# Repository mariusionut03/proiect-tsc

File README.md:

# OpenBook e-book reader

## BOM - Bill of Materials

| Device Module                       | Amount | Datasheet | Shop |
| ----------------------------------- | ------ | -------| --------|
| 112A-TAAR-R03_ATTEND                | 1      | https://www.attend.com.tw/en/product.php?act=view&id=253 | https://www.digikey.com/en/products/detail/attend-technology/112A-TAAR-R03/17633923 |
| BD5229G-TR                          | 1      | https://www.digikey.ph/en/products/detail/rohm-semiconductor/BD5229G-TR/658502 | https://www.digikey.ph/en/products/detail/rohm-semiconductor/BD5229G-TR/658502 |
| BUTTON_COSYOMV1                     | 3      | https://components101.com/switches/push-button | https://uk.farnell.com/wurth-elektronik/430182043816/switch-160gf-6x6mm-smd-4-3mm-act/dp/2065105?CMP=GRHB-OEMSECRETS101 |
| CPH3225A                            | 1      | https://www.digikey.com/en/products/detail/seiko-instruments/CPH3225A/8692444 | https://www.digikey.com/en/products/detail/seiko-instruments/CPH3225A/8692444 |
| DS3231SN                            | 1      | https://www.digikey.com/en/products/detail/analog-devices-inc-maxim-integrated/DS3231SN/1197576 | https://www.digikey.com/en/products/detail/analog-devices-inc-maxim-integrated/DS3231SN/1197576 |
| BME680                              | 1      | https://www.sparkfun.com/sparkfun-environmental-sensor-breakout-bme680-qwiic.html | https://www.sparkfun.com/sparkfun-environmental-sensor-breakout-bme680-qwiic.html |
| MCP73831                            | 1      | https://www.microchip.com/en-us/product/mcp73831 | https://www.microchipdirect.com/product/MCP73831T-2ADI/OT |
| C6-WROOM-1-N8                       | 1      | https://www.espressif.com/sites/default/files/documentation/esp32-c6-wroom-1_wroom-1u_datasheet_en.pdf | https://www.adafruit.com/product/5671 |
| FH34SRJ-24S-0.5SH_99_               | 1      | https://www.hirose.com/product/p/CL0580-1255-6-99 | https://www.hirose.com/product/p/CL0580-1255-6-99 |
| MAX17048G+T10                       | 1      | https://eu.mouser.com/ProductDetail/Analog-Devices-Maxim-Integrated/MAX17048G+T10?qs=D7PJwyCwLAoGnnn8jEPRBQ%3D%3D | https://eu.mouser.com/ProductDetail/Analog-Devices-Maxim-Integrated/MAX17048G+T10?qs=D7PJwyCwLAoGnnn8jEPRBQ%3D%3D |
| MBR0530                             | 3      | https://www.digikey.com/en/products/detail/onsemi/MBR0530/1048783 | https://www.digikey.com/en/products/detail/onsemi/MBR0530/1048783 |
| PGB1010603MR                        | 6      | https://www.digikey.com/en/products/detail/littelfuse-inc/PGB1010603MR/715755 | https://www.digikey.com/en/products/detail/littelfuse-inc/PGB1010603MR/715755 |
| SAMACSYS_PARTS_USB4110-GF-A         | 1      | https://www.digikey.ro/en/products/detail/gct/USB4110-GF-A/10384547 | https://www.digikey.ro/en/products/detail/gct/USB4110-GF-A/10384547 |
| SI1308EDL-T1-GE3                    | 1      | https://www.digikey.com/en/products/detail/vishay-siliconix/SI1308EDL-T1-GE3/4876435 | https://www.digikey.com/en/products/detail/vishay-siliconix/SI1308EDL-T1-GE3/4876435 |
| SJ                                  | 1      | https://www.digikey.com/en/products/detail/cui-devices/SJ1-3514N/738685 | https://www.digikey.com/en/products/detail/cui-devices/SJ1-3514N/738685 |
| USBLC6-2SC6Y                        | 1      | https://www.digikey.com/en/products/detail/stmicroelectronics/USBLC6-2SC6Y/2819177 | https://www.digikey.com/en/products/detail/stmicroelectronics/USBLC6-2SC6Y/2819177 |
| W25Q512JVEIQ                        | 1      | https://www.digikey.com/en/products/detail/winbond-electronics/W25Q512JVEIQ/10244706 | https://www.digikey.com/en/products/detail/winbond-electronics/W25Q512JVEIQ/10244706 |
| XC6220A331MR-G                      | 1      | https://www.digikey.com/en/products/detail/torex-semiconductor-ltd/XC6220B331MR-G/2138177 | https://www.digikey.com/en/products/detail/torex-semiconductor-ltd/XC6220B331MR-G/2138177 |
| SD0805S020S1R0                      | 2      | https://www.digikey.com/en/products/detail/kyocera-avx/SD0805S020S1R0/3749517 | https://www.digikey.com/en/products/detail/kyocera-avx/SD0805S020S1R0/3749517 |
| LTSPICE_C 100nF                     | 8      | https://www.digikey.com/en/products/detail/nextgen-components/0402B104K500HI/22601924 | https://www.digikey.com/en/products/detail/nextgen-components/0402B104K500HI/22601924 |
| LTSPICE_C 10nF                      | 1      | https://www.amazon.com/ALLECIN-Electrolytic-Capacitor-0-2x0-43in-Capacitors/dp/B0CMQC587X/ref=sr_1_1_sspa?sr=8-1-spons&sp_csd=d2lkZ2V0TmFtZT1zcF9hdGY&psc=1 | https://www.amazon.com/ALLECIN-Electrolytic-Capacitor-0-2x0-43in-Capacitors/dp/B0CMQC587X/ref=sr_1_1_sspa?sr=8-1-spons&sp_csd=d2lkZ2V0TmFtZT1zcF9hdGY&psc=1 |
| LTSPICE_C 4.7uF                     | 6      | https://www.amazon.com/ALLECIN-Electrolytic-Capacitor-0-2x0-43in-Capacitors/dp/B0CMQC587X/ref=sr_1_1_sspa?sr=8-1-spons&sp_csd=d2lkZ2V0TmFtZT1zcF9hdGY&psc=1 | https://www.amazon.com/ALLECIN-Electrolytic-Capacitor-0-2x0-43in-Capacitors/dp/B0CMQC587X/ref=sr_1_1_sspa?sr=8-1-spons&sp_csd=d2lkZ2V0TmFtZT1zcF9hdGY&psc=1 |
| LTSPICE_C 1uF                       | 10     | https://www.amazon.com/ALLECIN-Electrolytic-Capacitor-0-2x0-43in-Capacitors/dp/B0CMQC587X/ref=sr_1_1_sspa?sr=8-1-spons&sp_csd=d2lkZ2V0TmFtZT1zcF9hdGY&psc=1 | https://www.amazon.com/ALLECIN-Electrolytic-Capacitor-0-2x0-43in-Capacitors/dp/B0CMQC587X/ref=sr_1_1_sspa?sr=8-1-spons&sp_csd=d2lkZ2V0TmFtZT1zcF9hdGY&psc=1 |
| LTSPICE_C 0.1uF                     | 1      | https://www.digikey.com/en/products/detail/samsung-electro-mechanics/CL10E104KC8VPNC/20498486 | https://www.digikey.com/en/products/detail/samsung-electro-mechanics/CL10E104KC8VPNC/20498486 |
| ADAFRUIT_LED                        | 1      | https://www.adafruit.com/product/4684 | https://www.adafruit.com/product/4684 |
| ESP32_VARISTOR                      | 1      | https://uk.rs-online.com/web/p/varistors/9012743 | https://uk.rs-online.com/web/p/varistors/9012743 |
| CT3528 (RCL_CPOL-EU) 100uF          | 1      | https://www.datasheetarchive.com/?q=ct3528 |  |
| DMG2305UX-7 20V/4.2A/52mO/1.4W      | 2      | https://www.digikey.com/en/products/detail/diodes-incorporated/DMG2305UX-7/4340667 | https://www.digikey.com/en/products/detail/diodes-incorporated/DMG2305UX-7/4340667 |
| IND-4828-WE-TPC-WRE                 | 1      | https://www.axel-gl.com/en/asone/d/64-0172-48/ | https://www.axel-gl.com/en/asone/d/64-0172-48/ |
| JS-1MM(QWIIC_CONNECTOR)             | 1      | https://www.sparkfun.com/qwiic-jst-connector-smd-4-pin-horizontal.html | https://www.sparkfun.com/qwiic-jst-connector-smd-4-pin-horizontal.html |
| LTSPICE_R 5k1                       | 2      |  | https://www.amazon.com/BOJACK-Values-Resistor-Resistors-Assortment/dp/B08FD1XVL6/ref=sr_1_1_sspa?sr=8-1-spons&sp_csd=d2lkZ2V0TmFtZT1zcF9hdGY |
| LTSPICE_R 100k                      | 1      |  | https://www.amazon.com/BOJACK-Values-Resistor-Resistors-Assortment/dp/B08FD1XVL6/ref=sr_1_1_sspa?sr=8-1-spons&sp_csd=d2lkZ2V0TmFtZT1zcF9hdGY |
| LTSPICE_R 2.2                       | 1      |  | https://www.amazon.com/BOJACK-Values-Resistor-Resistors-Assortment/dp/B08FD1XVL6/ref=sr_1_1_sspa?sr=8-1-spons&sp_csd=d2lkZ2V0TmFtZT1zcF9hdGY |
| LTSPICE_R 10k                       | 16     |  | https://www.amazon.com/BOJACK-Values-Resistor-Resistors-Assortment/dp/B08FD1XVL6/ref=sr_1_1_sspa?sr=8-1-spons&sp_csd=d2lkZ2V0TmFtZT1zcF9hdGY |
| LTSPICE_R 0.47                      | 1      |  | https://www.amazon.com/BOJACK-Values-Resistor-Resistors-Assortment/dp/B08FD1XVL6/ref=sr_1_1_sspa?sr=8-1-spons&sp_csd=d2lkZ2V0TmFtZT1zcF9hdGY |
| LTSPICE_R 2k                        | 1      |  | https://www.amazon.com/BOJACK-Values-Resistor-Resistors-Assortment/dp/B08FD1XVL6/ref=sr_1_1_sspa?sr=8-1-spons&sp_csd=d2lkZ2V0TmFtZT1zcF9hdGY |
| LTSPICE_R 200                       | 1      |  | https://www.amazon.com/BOJACK-Values-Resistor-Resistors-Assortment/dp/B08FD1XVL6/ref=sr_1_1_sspa?sr=8-1-spons&sp_csd=d2lkZ2V0TmFtZT1zcF9hdGY |
| LTSPICE_R 15                        | 1      |  | https://www.amazon.com/BOJACK-Values-Resistor-Resistors-Assortment/dp/B08FD1XVL6/ref=sr_1_1_sspa?sr=8-1-spons&sp_csd=d2lkZ2V0TmFtZT1zcF9hdGY |
| Test Pad TP20R                      | 17     | https://us.misumi-ec.com/vona2/detail/221005496391/?HissuCode=TP20R-24 | https://us.misumi-ec.com/vona2/detail/221005496391/?HissuCode=TP20R-24 |

## ESP32-C6

- EN - RESET (Activare sau dezactivare device)
- IO0 - INT_RTC (Pin pentru intrerupere ale ceasului RTC sau Real Time Clock)
- IO1 - 32KHZ (Ofera o frecventa de 32 kHz, utilizata pentru sincronizare.)
- IO2 - MISO (Master In Slave Out, comunicare SPI pentru primire date de la periferice)
- IO3 - EPD_BUSY (Indica starea ecranului: ocupat sau liber)
- IO4 - SS_SD (Activeaza cardul SD, Slave Select)
- IO5 - EPD_DC (Control pentru date si comenzi ecran)
- IO6 - SCK (Serial Clock)
- IO7 - MOSI (Master Out Slave In, comunicare SPI pentru trimitere date la periferice)
- IO8 - GPIO8
- IO9 - IO/BOOT (Schimbare state dispozitiv)
- IO10 - EPD_CS (Select display)
- IO11 - FLASH_CS (Select memoria Flash)
- IO12 - USB_D- (comunicare USB)
- IO13 - USB_D+ (comunicare USB)
- IO15 - IO/CHANGE (navigare)
- IO16 - TX (Transmitere date)
- IO17 - RX (Receptie date)
- IO18 - RTC_RST (Reset RTC)
- IO19 - I2C_PW (Linia de alimentare pentru periferice I2C)
- IO20 - EPD_3V3_C (Alimentare)
- IO21 - SDA (I2C Data)
- IO22 - SCL (I2C Clock)
- IO23 - EPD_RST (Reset display)
- GND - Connected to ground 

## Randari

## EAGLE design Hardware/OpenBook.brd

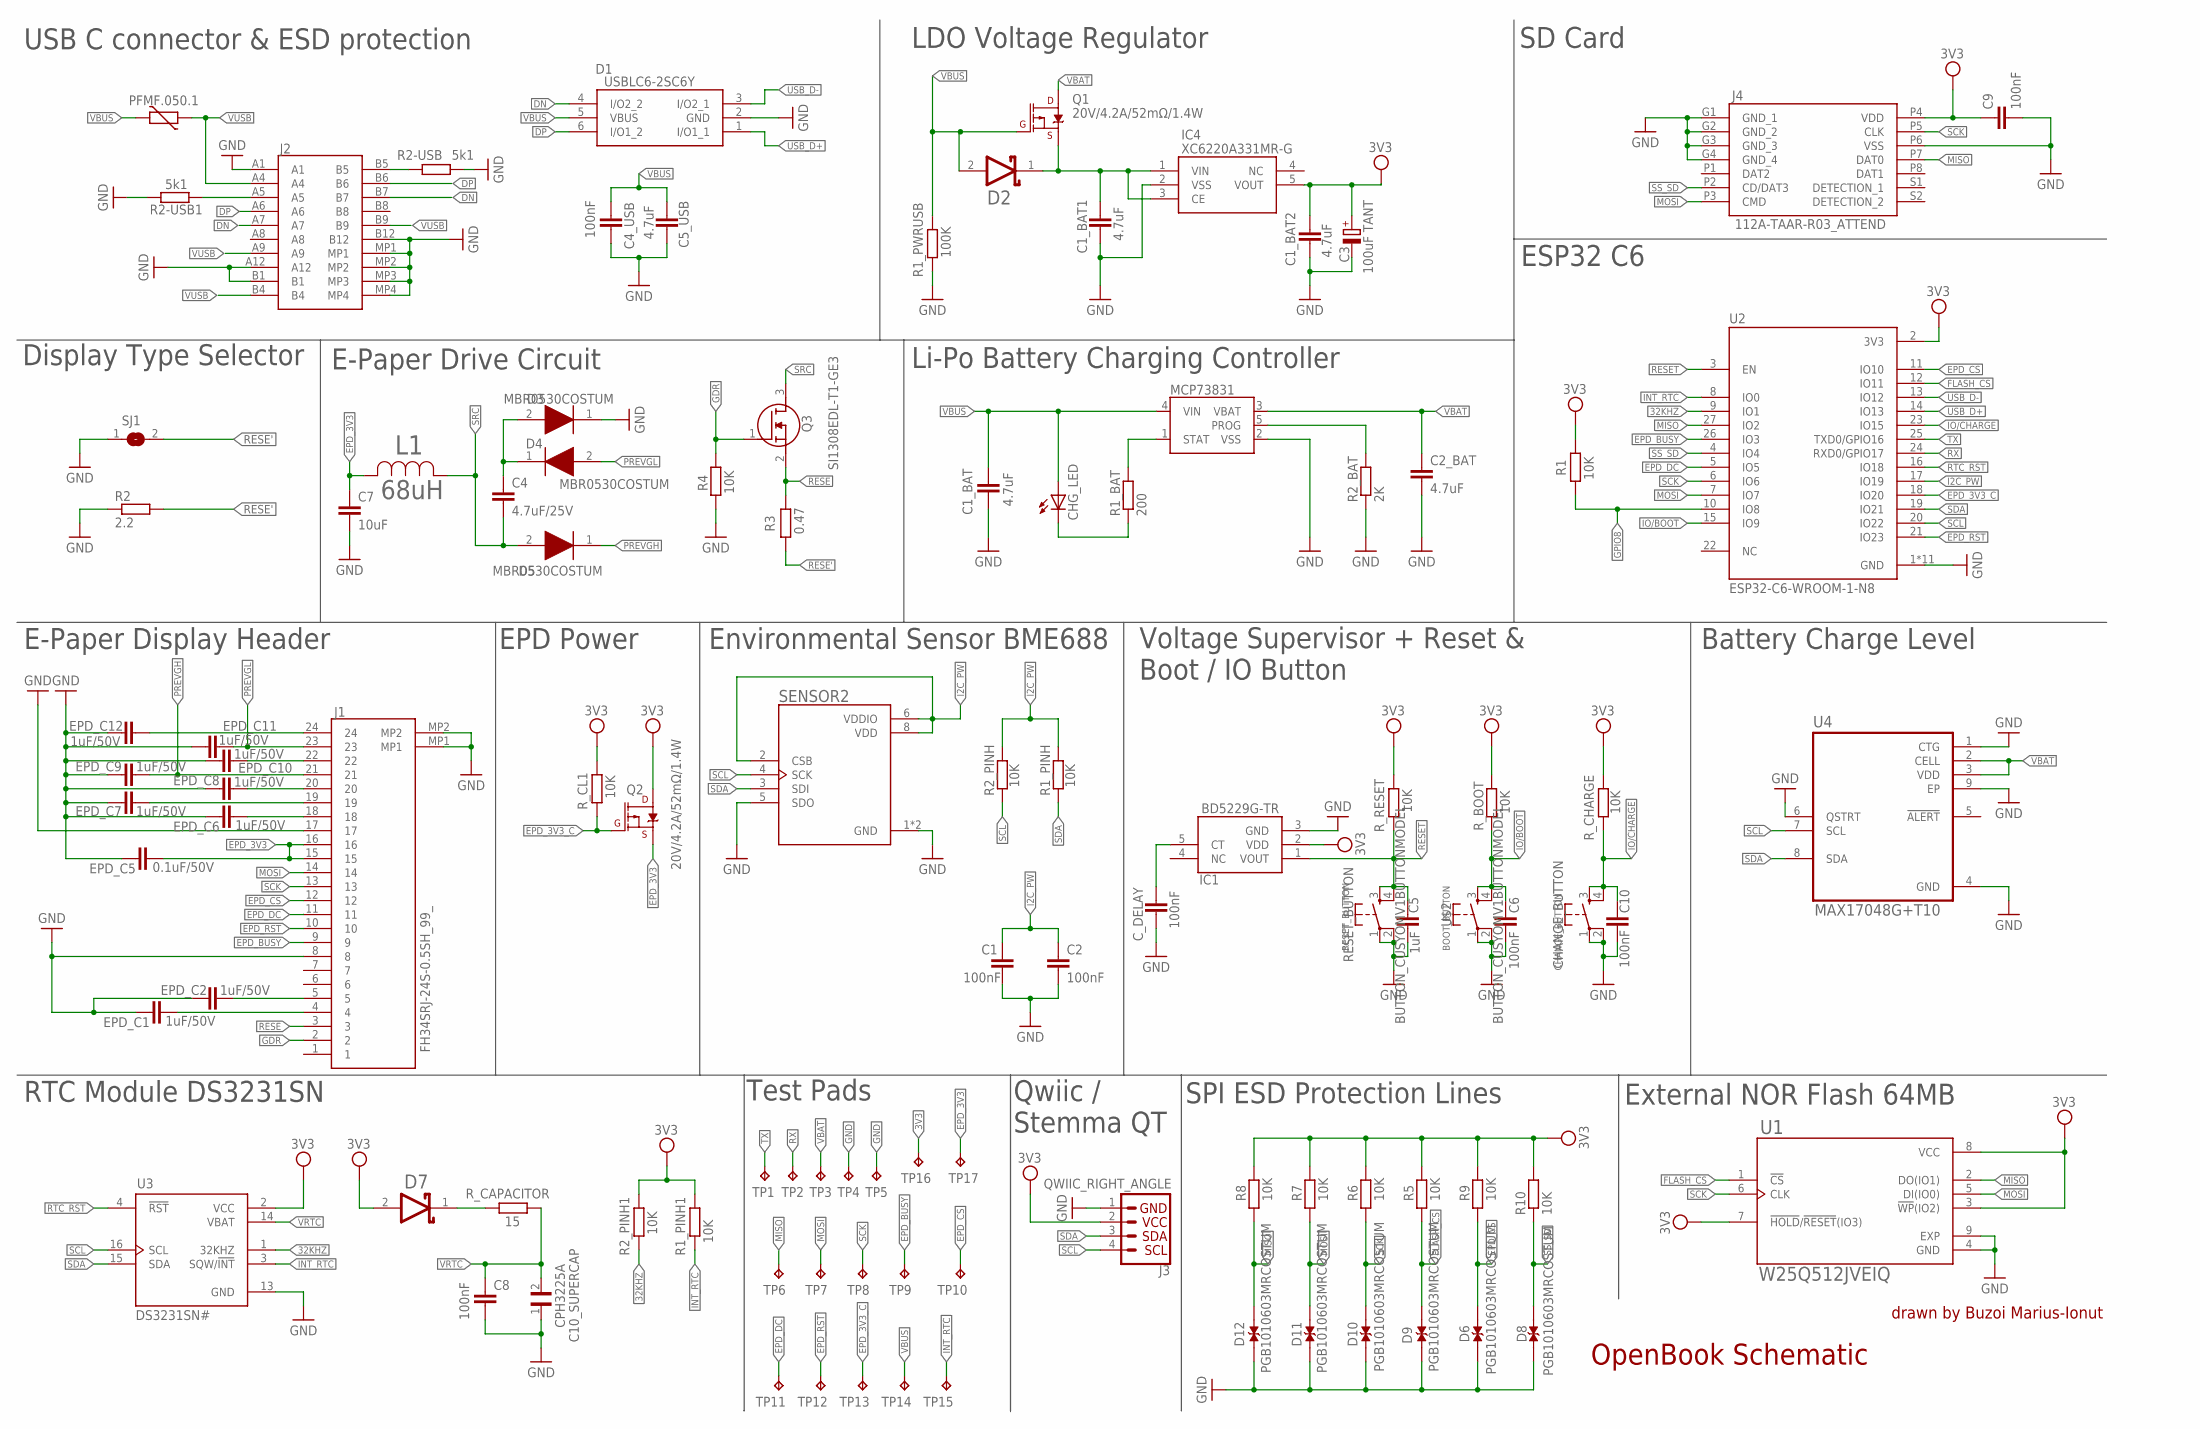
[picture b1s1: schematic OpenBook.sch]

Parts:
C1, C2, C4_USB, C6, C8, C9, C10: 100nF; ESP32_WROVER_EAGLE-LTSPICE_C0402
C1_BAT, C1_BAT1, C1_BAT2, C2_BAT, C5_USB: 4.7uF; ESP32_WROVER_EAGLE-LTSPICE_C0402
C3: 100uF TANT; RCL_CT3528
C4: 4.7uF/25V; ESP32_WROVER_EAGLE-LTSPICE_C0402
C5: 1uF; ESP32_WROVER_EAGLE-LTSPICE_C0402
C7: 10uF; ESP32_WROVER_EAGLE-LTSPICE_C0402
C10_SUPERCAP: CPH3225A; CAPCP3225X100N
CHANGE_BUTTON: BUTTON_CUSYOMV1BUTTONMODEL; MYBUTTON
CHG_LED: ADAFRUIT_LEDCHIP-LED0603; ADAFRUIT_CHIP-LED0603
C_DELAY: 100nF; ESP32_WROVER_EAGLE-LTSPICE_C0402
D1: USBLC6-2SC6Y; SOT95P280X145-6N
D2, D7: ESP32_WROVER_AVX---SD0805S020S1R0_AVX_SD0805S020S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; ESP32_WROVER_AVX---SD0805S020S1R0_AVX_SD0805S020S1R0_0
D3, D4, D5: MBR0530COSTUM; SOD3716X135N
D6, D8, D9, D10, D11, D12: PGB1010603MRCOSTUM; DIOC1608X36N
EPD_C1, EPD_C2, EPD_C6, EPD_C7, EPD_C8, EPD_C9, EPD_C10, EPD_C11, EPD_C12: 1uF/50V; ESP32_WROVER_EAGLE-LTSPICE_C0402
EPD_C5: 0.1uF/50V; ESP32_WROVER_EAGLE-LTSPICE_C0402
IC1: BD5229G-TR; SOT95P280X125-5N
IC4: XC6220A331MR-G; SOT95P280X120-5N
J1: FH34SRJ-24S-0.5SH_99_; FH34SRJ24S05SH99
J2: SAMACSYS_PARTS_USB4110-GF-A; SAMACSYS_PARTS_USB4110GFA
J3: QWIIC_RIGHT_ANGLE; JST04_1MM_RA
J4: 112A-TAAR-R03_ATTEND; 112ATAARR03ATTEND
L1: 68uH; IND_4828-WE-TPC_WRE
MCP73831: ESP32_WROVER_SPARKFUN-IC-POWER_MCP73831; ESP32_WROVER_SPARKFUN-IC-POWER_SOT23-5
PFMF.050.1: ESP32C6_VARISTORCN1812; ESP32C6_VARISTOR_CT/CN1812
Q1, Q2: 20V/4.2A/52mΩ/1.4W; ESP32_WROVER_SPARKFUN-DISCRETESEMI_SOT23-3
Q3: SI1308EDL-T1-GE3; SOT65P210X110-3N
R1, R1_PINH, R1_PINH1, R2_PINH, R2_PINH1, R4, R5, R6, R7, R8, R9, R10: 10K; ESP32_WROVER_EAGLE-LTSPICE_R0402
R1_BAT: 200; ESP32_WROVER_EAGLE-LTSPICE_R0402
R1_PWRUSB: 100K; ESP32_WROVER_EAGLE-LTSPICE_R0402
R2: 2.2; ESP32_WROVER_EAGLE-LTSPICE_R0402
R2-USB, R2-USB1: 5k1; ESP32_WROVER_EAGLE-LTSPICE_R0402
R2_BAT: 2K; ESP32_WROVER_EAGLE-LTSPICE_R0402
R3: 0.47; ESP32_WROVER_EAGLE-LTSPICE_R0402
RESET_BUTTON: BUTTON_CUSYOMV1BUTTONMODEL; MYBUTTON
R_BOOT: 10K; ESP32_WROVER_EAGLE-LTSPICE_R0402
R_CAPACITOR: 15; ESP32_WROVER_EAGLE-LTSPICE_R0402
R_CHARGE: 10K; ESP32_WROVER_EAGLE-LTSPICE_R0402
R_CL1: 10K; ESP32_WROVER_EAGLE-LTSPICE_R0402
R_RESET: 10K; ESP32_WROVER_EAGLE-LTSPICE_R0402
SENSOR2: ESP32_WROVER_BME680_BME680; ESP32_WROVER_BME680_PSON80P300X300X100-8N
SJ1: SJ
TP1, TP2, TP3, TP4, TP5, TP6, TP7, TP8, TP9, TP10, TP11, TP12, TP13, TP14, TP15, TP16, TP17: TP; TP20R
U1: W25Q512JVEIQ; SON127P600X800X80-9N
U2: ESP32-C6-WROOM-1-N8; XCVR_ESP32-C6-WROOM-1-N8
U3: DS3231SN#; SOIC127P1032X265-16N
U4: MAX17048G+T10; SON50P200X200X80-9N
U$2: BUTTON_CUSYOMV1BUTTONMODEL; MYBUTTON

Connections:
3V3: C1_BAT2.1, C3.+, C9.1, D7.2 (ANODE), IC1.2 (VDD), IC4.5 (VOUT), J3.2, J4.P4 (VDD), Q2.3 (D), R1.2, R1_PINH1.2, R2_PINH1.2, R5.2, R6.2, R7.2, R8.2, R9.2, R10.2, R_BOOT.2, R_CHARGE.2, R_CL1.2, R_RESET.2, TP16.TP, U1.3 (!WP!(IO2)), U1.7 (!HOLD!/!RESET!(IO3)), U1.8 (VCC), U2.2 (3V3), U3.2 (VCC)
32KHZ: R2_PINH1.1, U2.9 (IO1), U3.1 (32KHZ)
DN: D1.4 (I/O2_2), J2.A7, J2.B7
DP: D1.6 (I/O1_2), J2.A6, J2.B6
EPD_3V3: C7.1, EPD_C5.2, J1.15, J1.16, L1.2, Q2.2 (S), TP17.TP
EPD_3V3_C: Q2.1 (G), R_CL1.1, TP13.TP, U2.18 (IO20)
EPD_BUSY: J1.9, TP9.TP, U2.26 (IO3)
EPD_CS: D6.2, J1.12, R9.1, TP10.TP, U2.11 (IO10)
EPD_DC: J1.11, TP11.TP, U2.5 (IO5)
EPD_RST: J1.10, TP12.TP, U2.21 (IO23)
FLASH_CS: D9.2, R5.1, U1.1 (!CS), U2.12 (IO11)
GDR: J1.2, Q3.1 (G), R4.2
GND: C1.2, C1_BAT.2, C1_BAT1.2, C1_BAT2.2, C2.2, C2_BAT.2, C3.-, C4_USB.2, C5.2, C5_USB.2, C6.2, C7.2, C8.2, C9.2, C10.2, C10_SUPERCAP.1, CHANGE_BUTTON.1, CHANGE_BUTTON.2, C_DELAY.2, D1.2 (GND), D3.1 (K), D6.1, D8.1, D9.1, D10.1, D11.1, D12.1, EPD_C1.1, EPD_C2.1, EPD_C5.1, EPD_C6.1, EPD_C7.1, EPD_C8.1, EPD_C9.1, EPD_C10.1, EPD_C11.1, EPD_C12.1, IC1.3 (GND), IC4.2 (VSS), J1.8, J1.17, J1.MP1, J1.MP2, J2.A1, J2.A12, J2.B1, J2.B12, J2.MP1, J2.MP2, J2.MP3, J2.MP4, J3.1, J4.G1 (GND_1), J4.G2 (GND_2), J4.G3 (GND_3), J4.G4 (GND_4), J4.P6 (VSS), MCP73831.2 (VSS), R1_PWRUSB.1, R2.1, R2-USB.2, R2-USB1.1, R2_BAT.1, R4.1, RESET_BUTTON.1, RESET_BUTTON.2, SENSOR2.1 (GND), SENSOR2.5 (SDO), SENSOR2.7 (GND), SJ1.1, TP4.TP, TP5.TP, U1.4 (GND), U1.9 (EXP), U2.1 (GND), U2.28 (GND), U2.29_1 (GND), U2.29_2 (GND), U2.29_3 (GND), U2.29_4 (GND), U2.29_5 (GND), U2.29_6 (GND), U2.29_7 (GND), U2.29_8 (GND), U2.29_9 (GND), U3.13 (GND), U4.1 (CTG), U4.4 (GND), U4.6 (QSTRT), U4.9 (EP), U$2.1, U$2.2
GPIO8: R1.1, U2.10 (IO8)
I2C_PW: C1.1, C2.1, R1_PINH.2, R2_PINH.2, SENSOR2.2 (CSB), SENSOR2.6 (VDDIO), SENSOR2.8 (VDD), U2.17 (IO19)
INT_RTC: R1_PINH1.1, TP15.TP, U2.8 (IO0), U3.3 (SQW/!INT)
IO/BOOT: C6.1, R_BOOT.1, U2.15 (IO9), U$2.3, U$2.4
IO/CHARGE: C10.1, CHANGE_BUTTON.3, CHANGE_BUTTON.4, R_CHARGE.1, U2.23 (IO15)
MISO: D12.2, J4.P7 (DAT0), R8.1, TP6.TP, U1.2 (DO(IO1)), U2.27 (IO2)
MOSI: D11.2, J1.14, J4.P3 (CMD), R7.1, TP7.TP, U1.5 (DI(IO0)), U2.7 (IO7)
unnamed: J2.A5, R2-USB1.2
unnamed: C1_BAT1.1, D2.1 (CATHODE), IC4.1 (VIN), IC4.3 (CE), Q1.2 (S)
unnamed: MCP73831.1 (STAT), R1_BAT.2
unnamed: J2.B5, R2-USB.1
unnamed: CHG_LED.C, R1_BAT.1
unnamed: C4.1, D3.2 (A), D4.1 (K)
unnamed: EPD_C12.2, J1.24
unnamed: MCP73831.5 (PROG), R2_BAT.2
unnamed: C_DELAY.1, IC1.5 (CT)
unnamed: EPD_C10.2, J1.22
unnamed: EPD_C8.2, J1.20
unnamed: D7.1 (CATHODE), R_CAPACITOR.1
unnamed: EPD_C7.2, J1.19
unnamed: EPD_C6.2, J1.18
unnamed: EPD_C2.2, J1.5
unnamed: EPD_C1.2, J1.4
PREVGH: D5.1 (K), EPD_C9.2, J1.21
PREVGL: D4.2 (A), EPD_C11.2, J1.23
RESE: J1.3, Q3.2 (S), R3.2
RESE': R2.2, R3.1, SJ1.2
RESET: C5.1, IC1.1 (VOUT), RESET_BUTTON.3, RESET_BUTTON.4, R_RESET.1, U2.3 (EN)
RTC_RST: U2.16 (IO18), U3.4 (!RST)
RX: TP2.TP, U2.24 (RXD0/GPIO17)
SCK: D10.2, J1.13, J4.P5 (CLK), R6.1, TP8.TP, U1.6 (CLK), U2.6 (IO6)
SCL: J3.4, R2_PINH.1, SENSOR2.4 (SCK), U2.20 (IO22), U3.16 (SCL), U4.7 (SCL)
SDA: J3.3, R1_PINH.1, SENSOR2.3 (SDI), U2.19 (IO21), U3.15 (SDA), U4.8 (SDA)
SRC: C4.2, D5.2 (A), L1.1, Q3.3 (D)
SS_SD: D8.2, J4.P2 (CD/DAT3), R10.1, U2.4 (IO4)
TX: TP1.TP, U2.25 (TXD0/GPIO16)
USB_D+: D1.1 (I/O1_1), U2.14 (IO13)
USB_D-: D1.3 (I/O2_1), U2.13 (IO12)
VBAT: C2_BAT.1, MCP73831.3 (VBAT), Q1.3 (D), TP3.TP, U4.2 (CELL), U4.3 (VDD)
VBUS: C1_BAT.1, C4_USB.1, C5_USB.1, CHG_LED.A, D1.5 (VBUS), D2.2 (ANODE), MCP73831.4 (VIN), PFMF.050.1.2, Q1.1 (G), R1_PWRUSB.2, TP14.TP
VRTC: C8.1, C10_SUPERCAP.2, R_CAPACITOR.2, U3.14 (VBAT)
VUSB: J2.A4, J2.A9, J2.B4, J2.B9, PFMF.050.1.1

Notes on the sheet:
drawn by Buzoi Marius-Ionut
OpenBook Schematic
USB C connector & ESD protection
LDO Voltage Regulator
SD Card
Display Type Selector
E-Paper Drive Circuit
Li-Po Battery Charging Controller
ESP32 C6
E-Paper Display Header
EPD Power
Environmental Sensor BME688
Voltage Supervisor + Reset & Boot / IO Button
Battery Charge Level
RTC Module DS3231SN
Test Pads
Qwiic / Stemma QT
SPI ESD Protection Lines
External NOR Flash 64MB

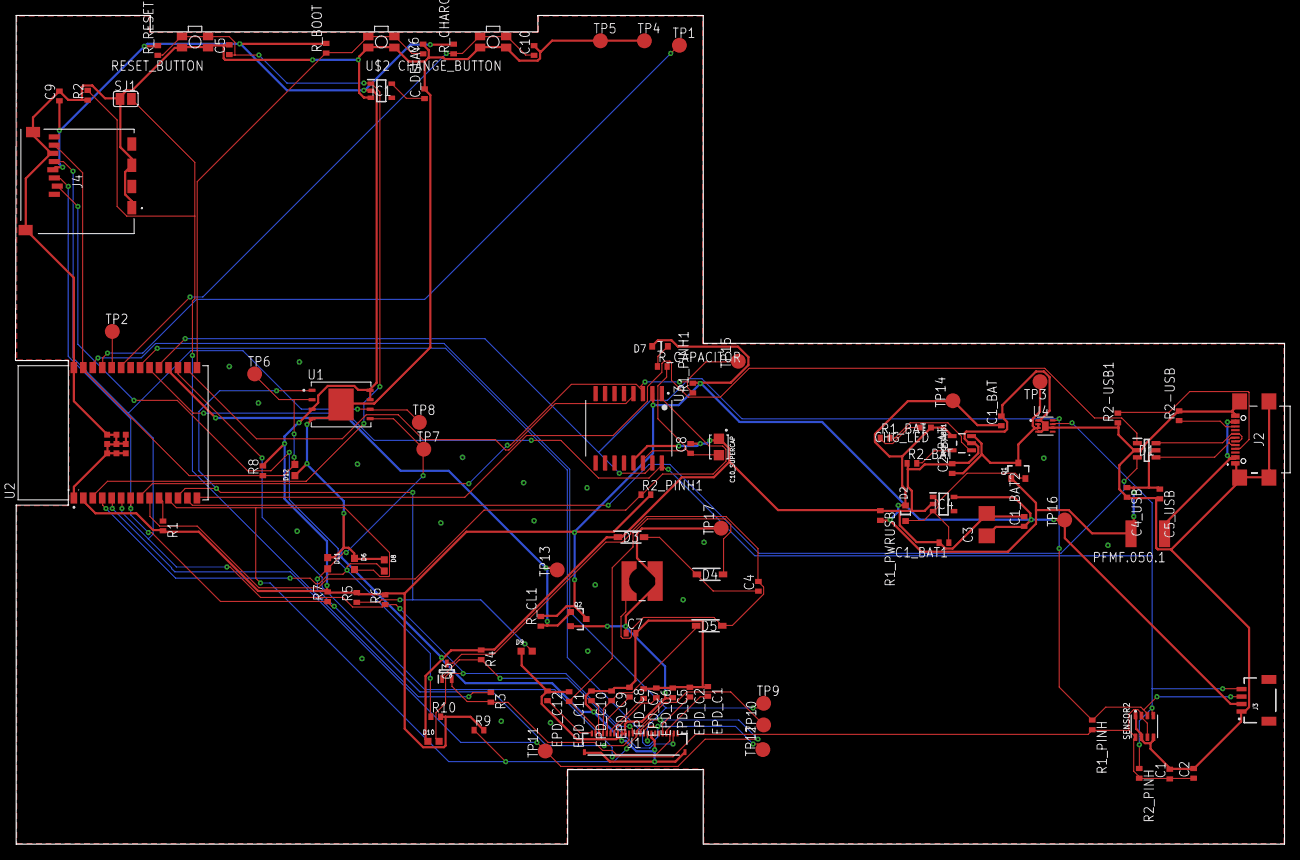
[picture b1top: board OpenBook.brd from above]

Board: 2 copper layers, 170.3 x 111.2 mm, 103 parts (0 on the bottom side), 55 nets.

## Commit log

2025-03-20 Device Schematic
2025-04-02 usbc/esd protection/ldo voltage sch + brd; board shape
2025-04-06 added project files
2025-04-13 Removed older versions; solved wrong components placing in PCB
2025-04-15 added 3d models for components; added render images
2025-04-15 Manufacturing files
2025-04-15 readme update

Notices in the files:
parts and their libraries:
COPYRIGHT: Copyright (C) 2024 Ultra Librarian. All rights reserved.
